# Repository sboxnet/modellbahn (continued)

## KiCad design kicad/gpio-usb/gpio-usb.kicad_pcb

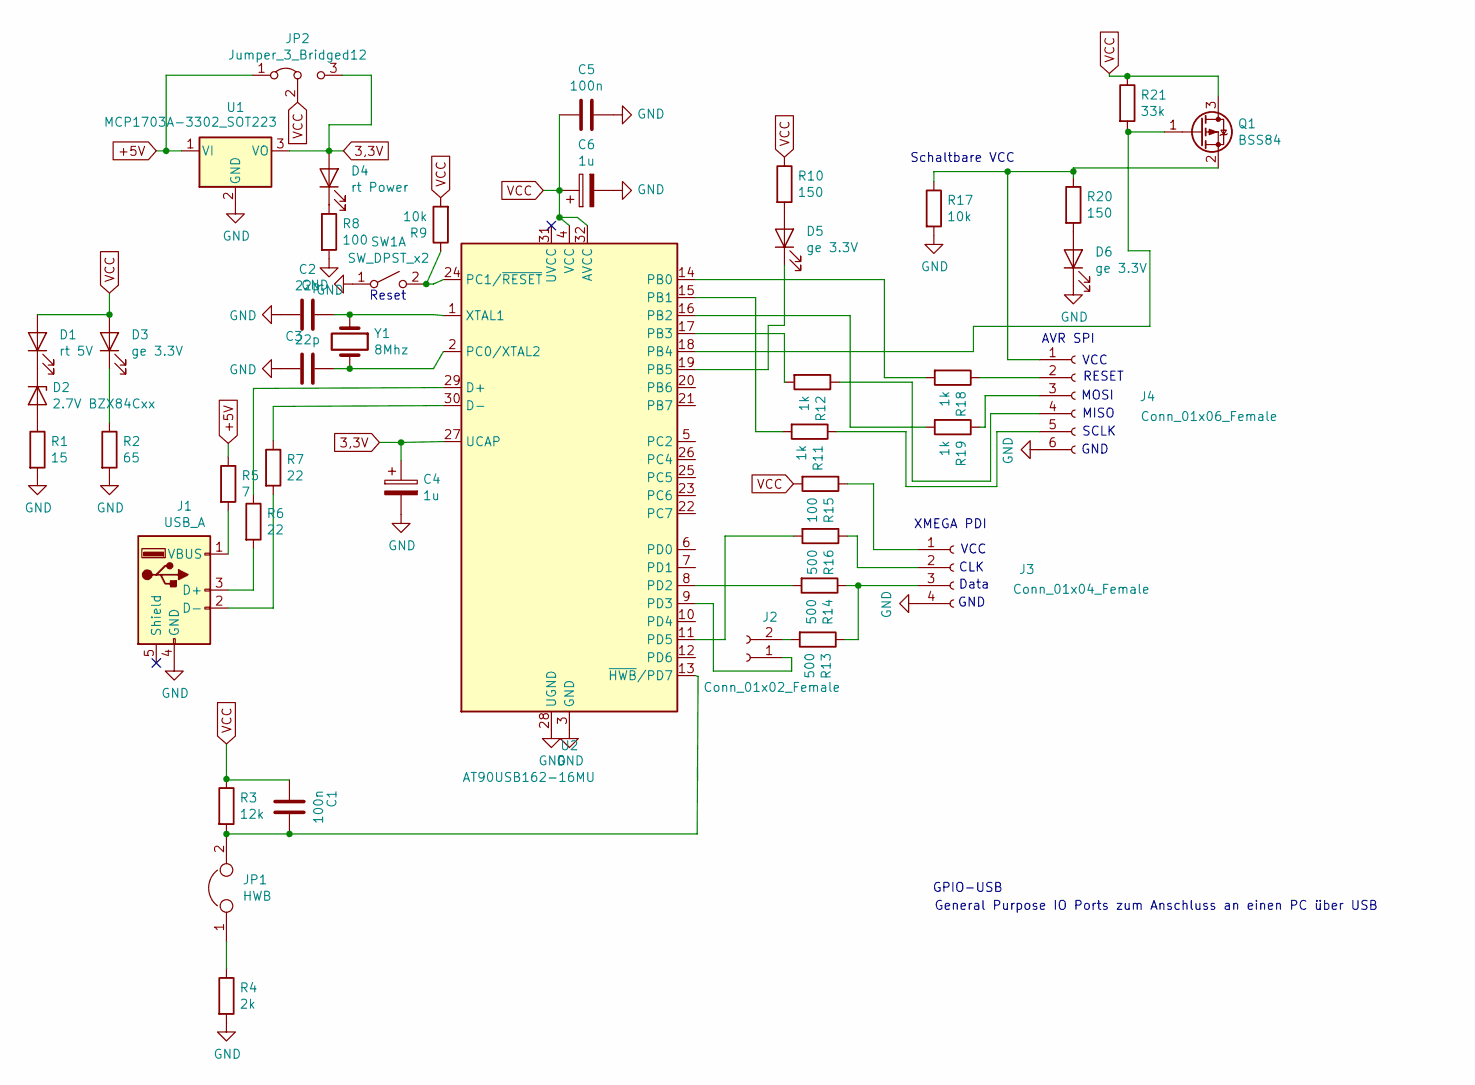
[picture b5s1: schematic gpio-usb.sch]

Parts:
C1: 100n; C_1206_3216Metric_Pad1.42x1.75mm_HandSolder
C2, C3: 22p; C_1206_3216Metric_Pad1.42x1.75mm_HandSolder
C4, C6: 1u; smd_cap_1206
C5: 100n; C_1206_3216Metric
D1: rt 5V; LED_0805_2012Metric
D2: 2.7V BZX84Cxx; D_SOT-23_ANK
D3, D5, D6: ge 3.3V; LED_0805_2012Metric
D4: rt Power; LED_0805_2012Metric
J1: USB_A; usbaassmann
J2: Conn_01x02_Female; PinHeader_1x02_P2.54mm_Vertical
J3: Conn_01x04_Female; PinHeader_1x04_P2.54mm_Vertical
J4: Conn_01x06_Female; PinHeader_1x06_P2.54mm_Vertical
JP1: HWB; jumper_2_male
JP2: Jumper_3_Bridged12; jumper_3_female
Q1: BSS84; SOT-23
R1: 15; R_1206_3216Metric
R2: 65; R_1206_3216Metric
R3: 12k; R_1206_3216Metric
R4: 2k; R_1206_3216Metric
R5: 7; R_1206_3216Metric
R6, R7: 22; R_1206_3216Metric
R8, R15: 100; R_1206_3216Metric
R9, R17: 10k; R_1206_3216Metric
R10, R20: 150; R_1206_3216Metric
R11, R12, R18, R19: 1k; R_1206_3216Metric
R13, R14, R16: 500; R_1206_3216Metric
R21: 33k; R_1206_3216Metric
SW1: SW_DPST_x2; PinHeader_1x02_P2.54mm_Vertical
U1: MCP1703A-3302_SOT223; SOT-223-3_TabPin2
U2: AT90USB162-16MU; QFN-32-1EP_5x5mm_P0.5mm_EP3.6x3.6mm
Y1: 8Mhz; Crystal_HC33-U_Vertical

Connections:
3,3V: C4.1, D4.2 (A), JP2.3 (B), U1.3 (VO), U2.27 (UCAP)
+5V: JP2.1 (A), R5.1, U1.1 (VI)
GND: C2.2, C3.2, C4.2, C5.1, C6.2, D6.1 (K), J1.4 (GND), J3.4, J4.6, R1.2, R2.2, R4.2, R8.2, R17.2, SW1.1 (A), U1.2 (GND), U2.3 (GND), U2.28 (UGND), U2.33 (GND)
unnamed: C1.1, JP1.2, R3.2, U2.13 (~HWB~/PD7)
unnamed: C2.1, U2.1 (XTAL1), Y1.1
unnamed: C3.1, U2.2 (PC0/XTAL2), Y1.2
unnamed: D1.1 (K), D2.1 (K)
unnamed: D2.2 (A), R1.1
unnamed: D3.1 (K), R2.1
unnamed: D4.1 (K), R8.1
unnamed: D5.1 (K), U2.19 (PB5)
unnamed: D5.2 (A), R10.2
unnamed: D6.2 (A), R20.2
unnamed: J1.1 (VBUS), R5.2
unnamed: J1.2 (D-), R7.2
unnamed: J1.3 (D+), R6.2
unnamed: J2.1, U2.9 (PD3)
unnamed: J2.2, R13.2
unnamed: J3.1, R15.1
unnamed: J3.2, R16.1
unnamed: J3.3, R13.1, R14.1
unnamed 22: J4.1, Q1.2 (S), R17.1, R20.1; also elsewhere on the board
unnamed: J4.2, R18.1
unnamed: J4.3, R19.1
unnamed: J4.4, R12.1
unnamed: J4.5, R11.1
unnamed: JP1.1, R4.1
unnamed: Q1.1 (G), R21.2, U2.18 (PB4)
unnamed: R6.1, U2.29 (D+)
unnamed: R7.1, U2.30 (D-)
unnamed: R9.1, SW1.2 (B), U2.24 (PC1/~RESET)
unnamed: R11.2, U2.15 (PB1)
unnamed: R12.2, U2.17 (PB3)
unnamed: R14.2, U2.8 (PD2)
unnamed: R16.2, U2.11 (PD5)
unnamed: R18.2, U2.14 (PB0)
unnamed: R19.2, U2.16 (PB2)
VCC: C1.2, C5.2, C6.1, D1.2 (A), D3.2 (A), JP2.2 (C), Q1.3 (D), R3.1, R9.2, R10.1, R15.2, R21.1, U2.4 (VCC), U2.32 (AVCC); also elsewhere on the board

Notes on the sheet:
Reset
GND
Data
CLK
VCC
XMEGA PDI
GPIO-USB
General Purpose IO Ports zum Anschluss an einen PC über USB
Schaltbare VCC
RESET
MOSI
MISO
SCLK
AVR SPI

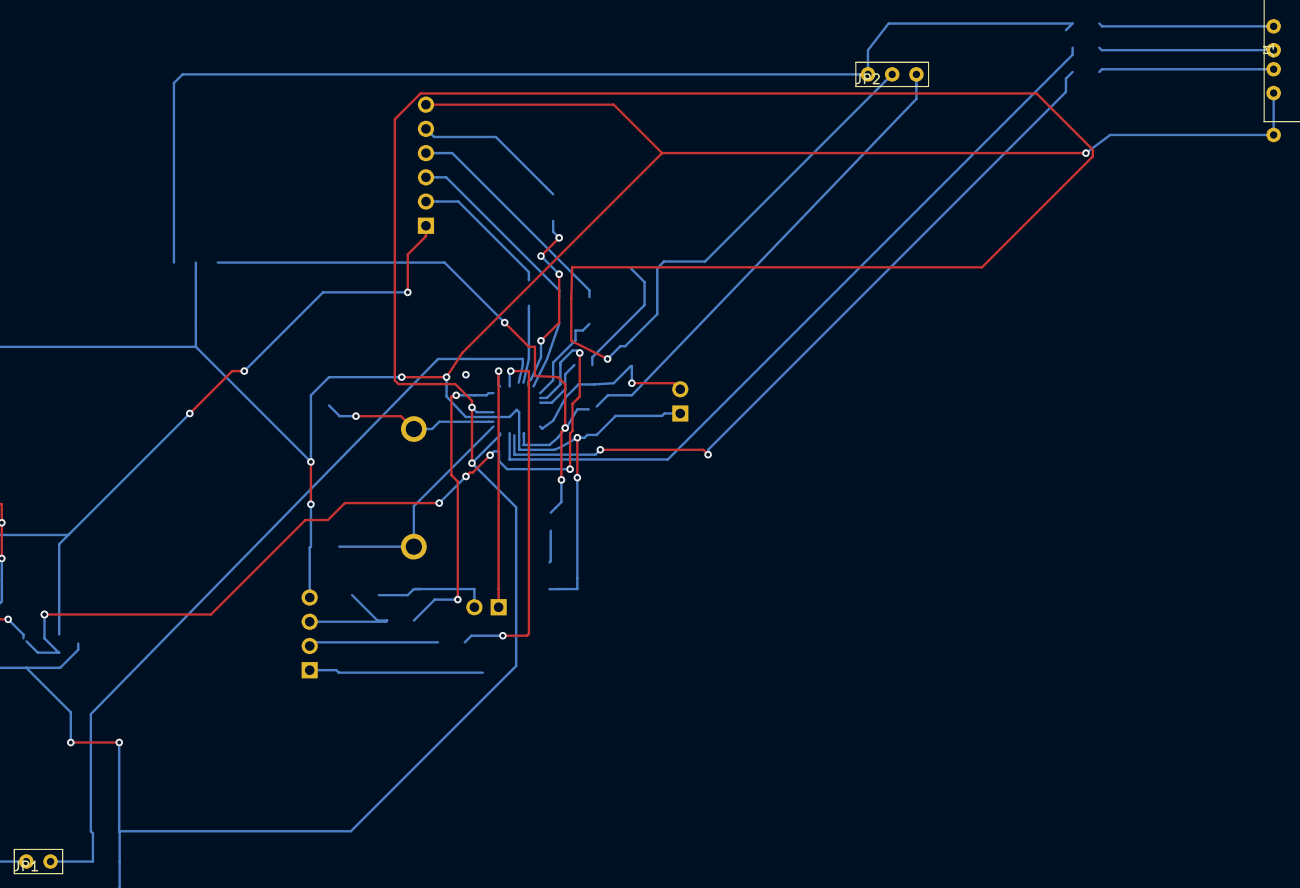
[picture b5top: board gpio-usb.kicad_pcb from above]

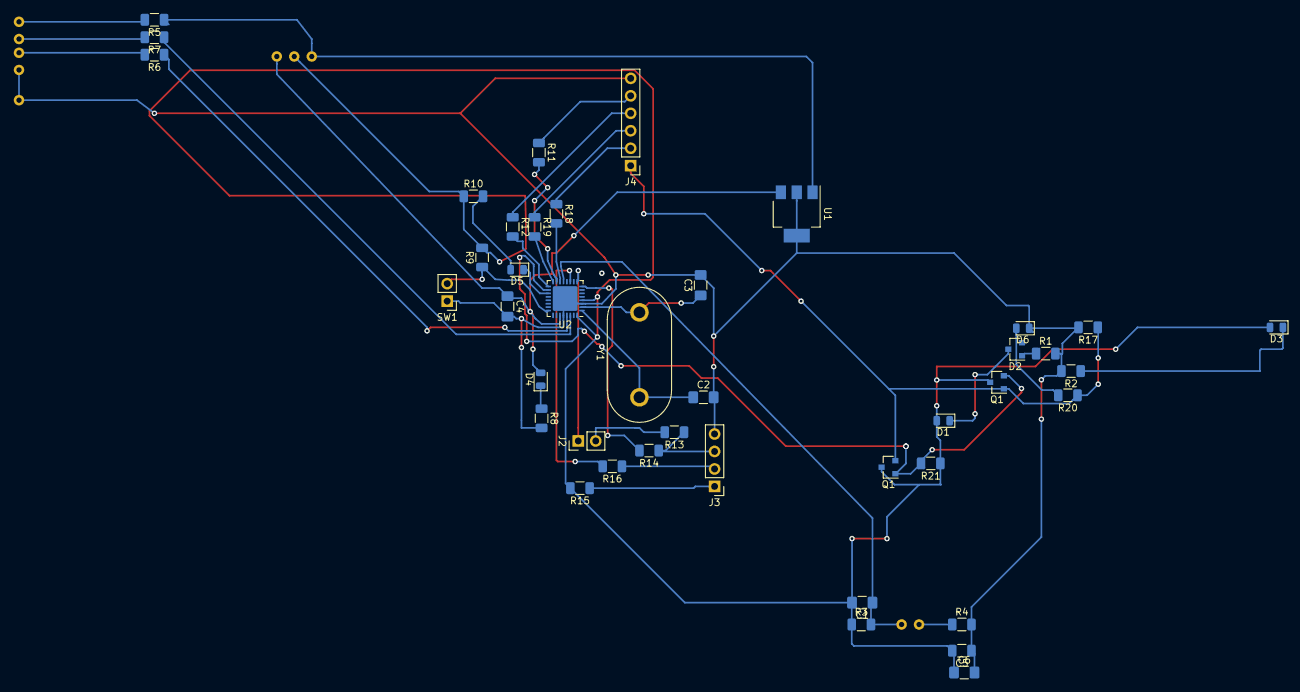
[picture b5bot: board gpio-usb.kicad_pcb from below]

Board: 2 copper layers, 45 parts (42 on the bottom side), 38 nets.

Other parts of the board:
Q1#2: BSS138; SOT-23

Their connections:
unnamed 22: Q1#2.1; also elsewhere on the board
VCC: Q1#2.3; also elsewhere on the board

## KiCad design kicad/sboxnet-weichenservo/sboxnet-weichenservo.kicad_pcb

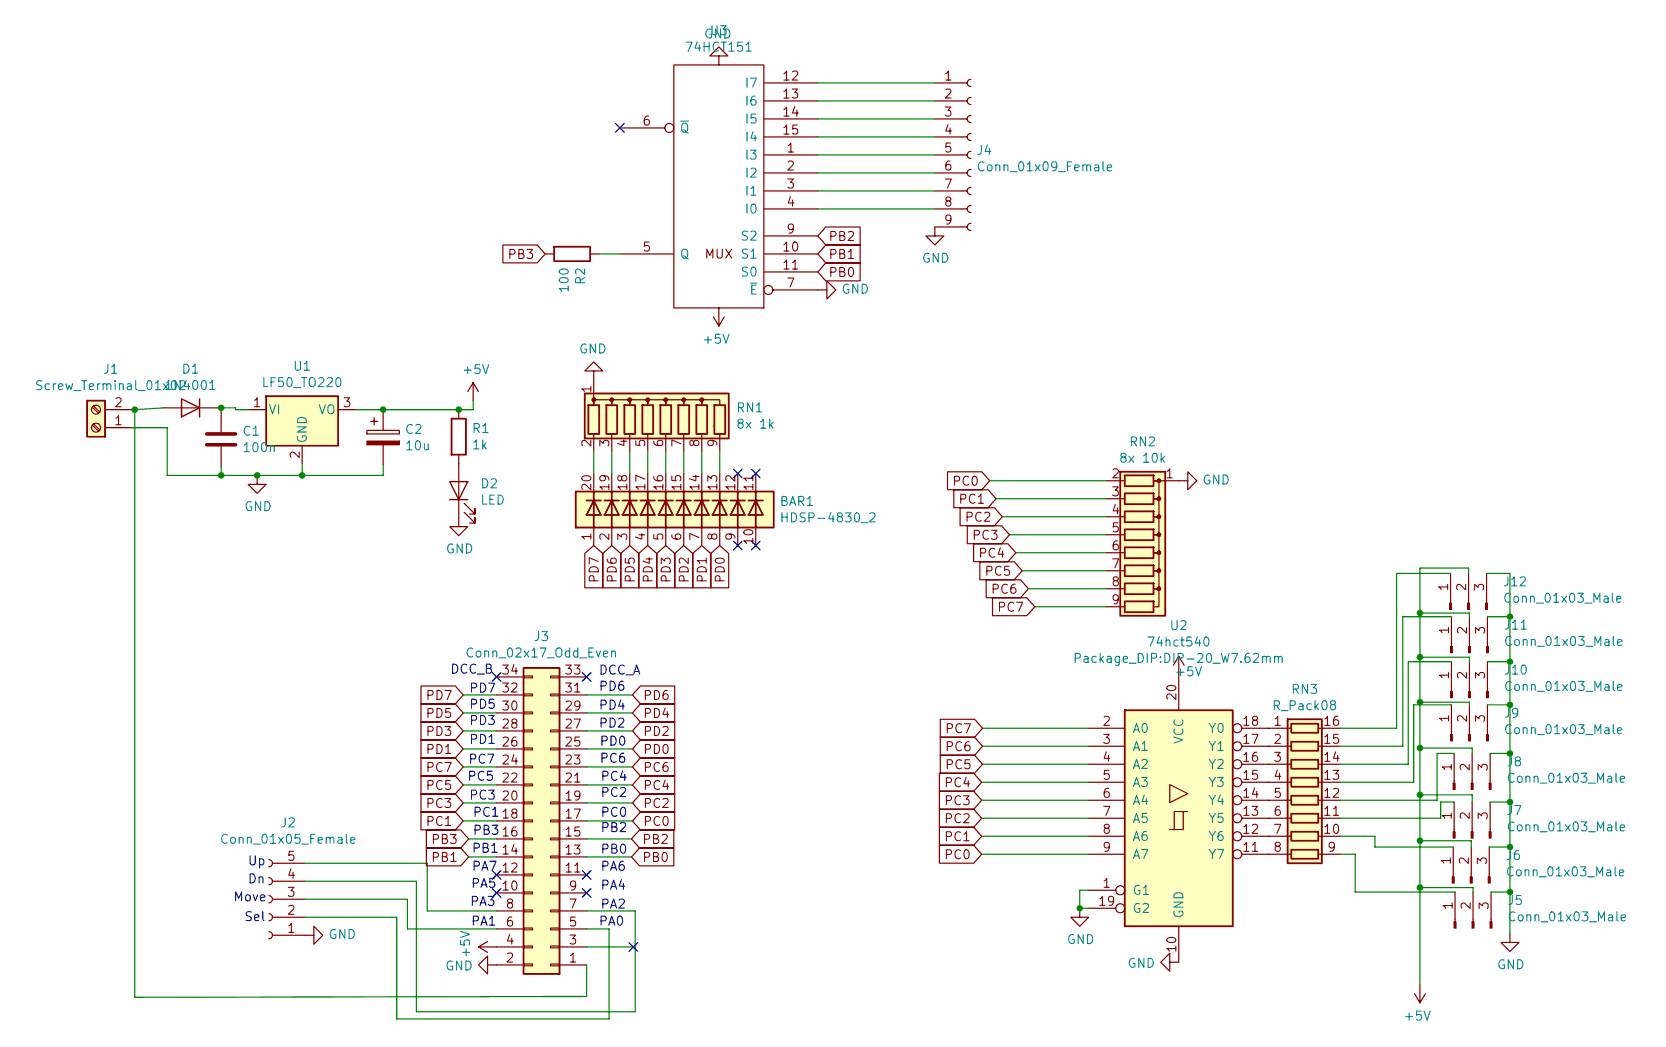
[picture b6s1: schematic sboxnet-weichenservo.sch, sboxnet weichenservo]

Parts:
BAR1: HDSP-4830_2; HDSP-4830
C1: 100n; C_Axial_L3.8mm_D2.6mm_P7.50mm_Horizontal
C2: 10u; CP_Axial_L10.0mm_D4.5mm_P15.00mm_Horizontal
D1: 1N4001; D_DO-41_SOD81_P10.16mm_Horizontal
D2: LED; LED_D3.0mm
J1: Screw_Terminal_01x02; TerminalBlock_Altech_AK300-2_P5.00mm
J2: Conn_01x05_Female; PinSocket_1x05_P2.54mm_Vertical
J3: Conn_02x17_Odd_Even; sboxnet-stecker-2x17
J4: Conn_01x09_Female; PinHeader_1x09_P2.54mm_Vertical
J5, J6, J7, J8, J9, J10, J11, J12: Conn_01x03_Male; PinHeader_1x03_P2.54mm_Vertical
R1: 1k; R_Axial_DIN0204_L3.6mm_D1.6mm_P5.08mm_Vertical
R2: 100; R_Axial_DIN0207_L6.3mm_D2.5mm_P5.08mm_Vertical
RN1: 8x 1k; R_Array_SIP9
RN2: 8x 10k; R_Array_SIP9
RN3: R_Pack08; DIP-16_W7.62mm
U1: LF50_TO220; TO-220-3_Vertical
U2: 74hct540; DIP-20_W7.62mm
U3: 74HCT151; DIP-16_W7.62mm_Socket

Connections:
+5V: C2.1, J3.4, J5.2, J6.2, J7.2, J8.2, J9.2, J10.2, J11.2, J12.2, R1.1, U1.3 (VO), U2.20 (VCC), U3.16 (VCC)
GND: C1.2, C2.2, D2.1 (K), J1.1, J2.1, J3.2, J4.9, J5.3, J6.3, J7.3, J8.3, J9.3, J10.3, J11.3, J12.3, RN1.1 (common), RN2.1 (common), U1.2 (GND), U2.1 (G1), U2.10 (GND), U2.19 (G2), U3.7 (~E), U3.8 (GND)
unnamed: BAR1.13 (K), RN1.9 (R8)
unnamed: BAR1.14 (K), RN1.8 (R7)
unnamed: BAR1.15 (K), RN1.7 (R6)
unnamed: BAR1.16 (K), RN1.6 (R5)
unnamed: BAR1.17 (K), RN1.5 (R4)
unnamed: BAR1.18 (K), RN1.4 (R3)
unnamed: BAR1.19 (K), RN1.3 (R2)
unnamed: BAR1.20 (K), RN1.2 (R1)
unnamed: C1.1, D1.1 (K), U1.1 (VI)
unnamed: D1.2 (A), J1.2, J3.1
unnamed: D2.2 (A), R1.2
unnamed: J2.2, J3.5
unnamed: J2.3, J3.6
unnamed: J2.4, J3.7
unnamed: J2.5, J3.8
unnamed: J4.1, U3.12 (I7)
unnamed: J4.2, U3.13 (I6)
unnamed: J4.3, U3.14 (I5)
unnamed: J4.4, U3.15 (I4)
unnamed: J4.5, U3.1 (I3)
unnamed: J4.6, U3.2 (I2)
unnamed: J4.7, U3.3 (I1)
unnamed: J4.8, U3.4 (I0)
unnamed: J5.1, RN3.9 (R8.2)
unnamed: J6.1, RN3.10 (R7.2)
unnamed: J7.1, RN3.11 (R6.2)
unnamed: J8.1, RN3.12 (R5.2)
unnamed: J9.1, RN3.13 (R4.2)
unnamed: J10.1, RN3.14 (R3.2)
unnamed: J11.1, RN3.15 (R2.2)
unnamed: J12.1, RN3.16 (R1.2)
unnamed: R2.1, U3.5 (Q)
unnamed: RN3.1 (R1.1), U2.18 (Y0)
unnamed: RN3.2 (R2.1), U2.17 (Y1)
unnamed: RN3.3 (R3.1), U2.16 (Y2)
unnamed: RN3.4 (R4.1), U2.15 (Y3)
unnamed: RN3.5 (R5.1), U2.14 (Y4)
unnamed: RN3.6 (R6.1), U2.13 (Y5)
unnamed: RN3.7 (R7.1), U2.12 (Y6)
unnamed: RN3.8 (R8.1), U2.11 (Y7)
PB0: J3.13, U3.11 (S0)
PB1: J3.14, U3.10 (S1)
PB2: J3.15, U3.9 (S2)
PB3: J3.16, R2.2
PC0: J3.17, RN2.2 (R1), U2.9 (A7)
PC1: J3.18, RN2.3 (R2), U2.8 (A6)
PC2: J3.19, RN2.4 (R3), U2.7 (A5)
PC3: J3.20, RN2.5 (R4), U2.6 (A4)
PC4: J3.21, RN2.6 (R5), U2.5 (A3)
PC5: J3.22, RN2.7 (R6), U2.4 (A2)
PC6: J3.23, RN2.8 (R7), U2.3 (A1)
PC7: J3.24, RN2.9 (R8), U2.2 (A0)
PD0: BAR1.8 (A), J3.25
PD1: BAR1.7 (A), J3.26
PD2: BAR1.6 (A), J3.27
PD3: BAR1.5 (A), J3.28
PD4: BAR1.4 (A), J3.29
PD5: BAR1.3 (A), J3.30
PD6: BAR1.2 (A), J3.31
PD7: BAR1.1 (A), J3.32

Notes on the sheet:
PA0
PA2
PA4
PA6
PB0
PB2
PC0
PC2
PC4
PC6
PD0
PD2
PD4
PD6
DCC_A
PA1
PA3
PA5
PA7
PB3
PC1
PC3
PC5
PC7
PD1
PD3
PD5
PD7
DCC_B
Move
Sel
PB1

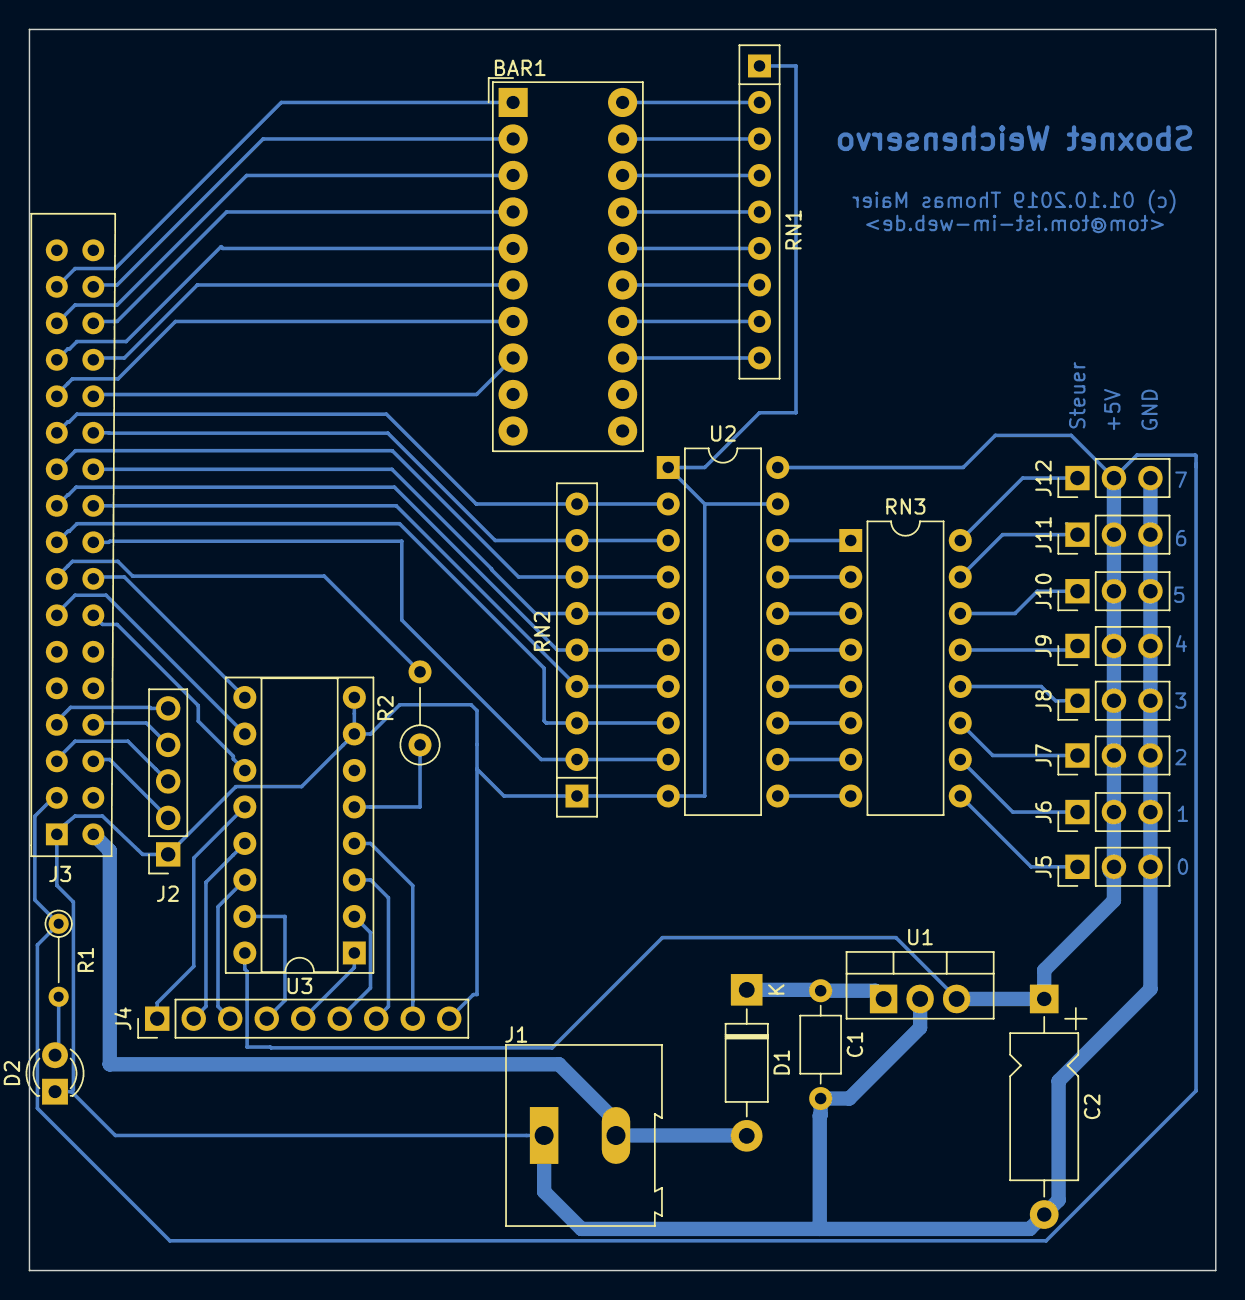
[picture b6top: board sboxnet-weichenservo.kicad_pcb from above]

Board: 2 copper layers, 82.5 x 86.4 mm, 25 parts (0 on the bottom side), 62 nets.

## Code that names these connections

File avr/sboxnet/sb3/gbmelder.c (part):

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
// für neue Hardware!
void show_besetzt_leds(void) {
	// PC6 (Bit 0) und PC7 (Bit 1)
	// PD0..PD7(Bit 2 .. 9)
	// zuerst mal alles aus
	port_clr(PORTC, Bit(6)|Bit(7));
	port_out(PORTD) = 0;
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
void do_init_system(void) {
	// Erst Hardware prüfen
	// PORTB auf Input: PB0..PB3
	port_dirin(PORTB, 0x0f);
	// und Eingabe überprüfen
	uint8_t pbin = port_in(PORTB);
	// ist PB0 und PB2 auf Low, PB1 und PB3 auf High ==> neue Hardware
	if (bit_is_set(pbin, 2) && bit_is_clear(pbin, 1) && bit_is_clear(pbin, 3)) {
		// neue Hardware
		hardwaretyp = 1;
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	switch(hardwaretyp) {
		case 1: {
            // Port für LEDs: im Gegensatz zur alten Hardware wird hier nicht multiplexed, sondern direkt LEDs angesteuert
            // PD0..PD7(Bit 2 .. 9)
			port_out(PORTD) = 0; // PORTD = 0
			port_dirout(PORTD, 0xff); // PORTD as output
			PORTCFG_MPCMASK = 0xff; // Alle Pins
			PORTD.PIN0CTRL = PORT_OPC_TOTEM_gc; // Alle PORTD Pins auf TOTEM Pole
			// PC6 (Bit 0) und PC7 (Bit 1)
			port_dirout(PORTC, Bit(6) | Bit(7)); // PC6 and PC7 as output
            PORTCFG_MPCMASK = 0xc0;
            PORTC.PIN0CTRL = PORT_OPC_TOTEM_gc;

            // PORTA als Input (PA0..PA7) (Bit 0 .. 7)
            port_dirin(PORTA, 0xff);
            // PC0 (Bit 8), PC1 (Bit 9) als Eingabe
            port_dirin(PORTC, 0x3);

			break;
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    // Sensoren Init mit 0 == Nichts belegt
    memset(g_sensors, 0, sizeof(g_sensors));
    
    // PB0  DCC Signal Pin

    // PB0 PullDown, beide Flanken
    DCCSENSE_PORT.PIN0CTRL = PORT_OPC_PULLDOWN_gc|PORT_ISC_BOTHEDGES_gc;
    //PORTB.PIN0CTRL = PORT_OPC_PULLDOWN_gc|PORT_ISC_BOTHEDGES_gc;
    // Decoder Init PortB0
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
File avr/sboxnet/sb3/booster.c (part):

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// LED Port
#define LED_PORT  PORTD
// Bits für LEDs
#define LED_NOTAUS_b      0 // Notaus
#define LED_CUR_OV_b      1 // Strom zu hoch
#define LED_CUR_SHORT_b   2 // Kurzschluss
#define LED_BO_ON_b       3 // Booster EIN
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#define DCCM_IN2_b  1 // IN2
#define DCCM_OV_b   3 // OV
#define DCCM_DCCIN_b  4
#define DCCM_NOTAUS_b 5 // NOTAUS
//#define DCCM_CUTOUT_b 7

// Strom zu hoch detektor: PORT
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//#define CUR_OV_b   3

// Booster NOTAUS betätigt: PORT
//#define NOTAUS_PORT  PORTC
// und Bit:
//#define NOTAUS_b   5

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// g_advals[2] Booster Strom 2
static uint16_t g_advals[3] = { 0, 0, 0 };

// Notaus PC5
#define SWITCH_NOTAUS_b  0
// Button zwischenspeichern für Entprellung
static uint8_t g_switches = 0;
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
// Booster Flags
#define BOOSTER_FLG_ON_b      0 // Booster ist EIN
#define BOOSTER_FLG_NOTAUS_b  1 // Booster NOTAUS
#define BOOSTER_FLG_CUR_OV_b  2 // Booster Strom zu hoch
static uint8_t g_booster_flags = 0; // Booster Flags

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 * Kurzschluss Sensor aus
 */
void dcc_sensors_off(void) {
    // PC3 Sensor Interrupt aus: PORTC INT0
    DCCM_PORT.INTCTRL = (PORTC.INTCTRL & ~PORT_INT0LVL_gm) | PORT_INT0LVL_OFF_gc;
    // Kein PORTC INT0 mehr
    DCCM_PORT.INT0MASK = 0; // L6206 Stromüberwachung
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    DCCM_PORT.INTFLAGS = Bit(PORT_INT0IF_bp); // clear interrupt flags;
    
    DCCM_PORT.INTCTRL = (PORTC.INTCTRL & ~PORT_INT0LVL_gm) | PORT_INT0LVL_OFF_gc;
    // DCCM_OV_b (PC3) auf Falling Edge
    DCCM_PORT.PIN3CTRL = PORT_ISC_FALLING_gc;
    
    // Anzahl Kurzschlüsse zurücksetzen
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        // DCC IN Interrupt
        // DCCM_PORT.DCCM_DCCIN_b als PORTC Int1
        DCCM_PORT.INT1MASK = Bit(DCC_IN_b);
        // PC4 beidseitige Flanke
        DCCM_PORT.PIN4CTRL = PORT_ISC_BOTHEDGES_gc;
        // INT1 Flag löschen
        DCCM_PORT.INTFLAGS = Bit(PORT_INT1IF_bp);
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        g_timer_startup = TIMER_STARTUP;

        // DCC IN Init
        // Status von PC4 (DCCM_IN_b) H?
        if (bit_is_set(port_in(DCC_IN_PORT), DCC_IN_b)) {
            // dann Brücke init mit
            port_setbit(DCCM_PORT, DCCM_IN1_b); // IN1 als H
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    port_clrbit(LED_PORT, LED_NOTAUS_b);
}

/* Port PC3 (Stromabschaltung)
 * 
 * Kurzschluss LED kurz aufleuchten, Kurzschlusszähler erhöhen.
 */
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 * DCC Signal aus.
 */
static NOINLINE void dcc_signal_disable(void) {
    // Bit DCCM_EN_b (PC2) aus
    port_clrbit(DCCM_PORT, DCCM_EN_b);
    // 2us warten
    _delay_us(2);
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static NOINLINE void dcc_signal_enable(void) {
    // 1us warten
    _delay_us(1);
    // Bit DCCM_EN_b (PC2) ein
    port_setbit(DCCM_PORT, DCCM_EN_b);
}

/* DCC Input Signal: PORTC.PC4 port Interrupt
 * PORTC.PC4 reagiert auf beide Flanken.
 *
 */
ISR(PORTC_INT1_vect) { // DCC Input Signal
    // ist PORTC.PC4 gesetzt?
    if (bit_is_set(port_in(DCC_IN_PORT), DCC_IN_b)) {
        // webb H, dann erst disable
        dcc_signal_disable();
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
/* void measure_task(void)
 * Durchführung der Strom und Spannungsmessung.
 * PA0, PA2 Strommessung: U = 0.22 * I; 0.22 * 1A = 0.22 V, 0.22 * 2A = 0.44V, 0.22 * 3A = 0.66V: 0,22 * 2.4A= 0,528V
 *     bei Rcl = 10kOhm Stromabschaltung bei ca 2,3 A
 * PA1 Spannungsmessung Vmess = 0.05982 * V bei 15 V -> 0,8974 V
 */
static void measure_task(void) {
    // sind alle ADCA Kanele bereit
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    // LED_PORT auf Ausgabe
    port_dirout(PORTD, 0x0f);
    // LED_PORTs auf totem pole
    PORTCFG_MPCMASK = 0x0f; // PD2..0
    PORTD.PIN0CTRL = PORT_OPC_TOTEM_gc;
    
    // DCCM_PORT
    // alles OFF vorbereiten
    port_out(DCCM_PORT) = 0;
    // PC0 (IN1), PC1(IN2), PC2 (EN) als Ausgabe
    port_dirout(DCCM_PORT, Bit(DCCM_EN_b)|Bit(DCCM_IN2_b)|Bit(DCCM_IN1_b));
    // PC3(OV), PC4 (DCCIN), PC5(NOTAUS) als Eingabe
    port_dirin(DCCM_PORT, Bit(DCCM_OV_b)|Bit(DCCM_DCCIN_b)|Bit(DCCM_NOTAUS_b));
    // Ausgabe ports als totem pole
    PORTCFG_MPCMASK = Bit(DCCM_EN_b)|Bit(DCCM_IN2_b)|Bit(DCCM_IN1_b);
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
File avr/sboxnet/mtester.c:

#include "common.h"
#include "sboxnet-struct.h"

#define DEVICE_DESC "ModulTester"
#define PRODUCT_ID   0xa123
#define VENDOR_ID    0x5566
#define FIRMWARE_VERSION 0x0200


APP_FIRMWARE_HEADER(PRODUCT_ID, VENDOR_ID, FIRMWARE_VERSION)

/* timer TCC1
 */

#define TIMER_PERIOD (32000000 / 1024 -1) // = 31250-1

#define NUM_STEPS 3
// wird bei jedem TCC0 OV um eins verringert
volatile int8_t step = NUM_STEPS-1;

// TCC0 overflow 
ISR(TCC1_OVF_vect) {
    step--;
    if (step < 0) {
        step = NUM_STEPS-1;
    }
}


// do_init_system: device system init
// return none
void do_init_system(void) {
    // alle Ports auf Output
    port_out(PORTA) = 0x0;
    port_dirout(PORTA, 0xff); // PORTA as output
    PORTCFG_MPCMASK = 0xff;
    PORTA.PIN0CTRL = PORT_OPC_TOTEM_gc; // all PORTA Pins to TOTEM 
    
    port_out(PORTB) = 0x0;
    port_dirout(PORTB, 0xff); // PORTB as output
    PORTCFG_MPCMASK = 0xff; // all pin
    PORTB.PIN0CTRL = PORT_OPC_TOTEM_gc; // all PORTB Pins to TOTEM 
    
    port_out(PORTC) = 0x0;
    port_dirout(PORTC, 0xff); // PORTC as output
    PORTCFG_MPCMASK = 0xff; // all pin
    PORTC.PIN0CTRL = PORT_OPC_TOTEM_gc; // all PORTC Pins to TOTEM 
    
    port_out(PORTD) = 0x0;
    port_dirout(PORTD, 0xff); // PORTD as output
    PORTCFG_MPCMASK = 0xff; // all pin
    PORTD.PIN0CTRL = PORT_OPC_TOTEM_gc; // all PORTD Pins to TOTEM
    
    //port_set(PORTD, Bit(5));
    //port_set(PORTD, Bit(4));
    
    // set paramters written to EEPROM from common area g_com
    // set Product ID
    g_com.productid = PRODUCT_ID;
    // set VENDOR_ID
    g_com.vendorid = VENDOR_ID;
    // set Firmware Version
    g_com.firmware_version = FIRMWARE_VERSION;
    // Fähigkeiten
    g_com.capabilities = CAP_TESTER;
    // Fähigkeit.Klasse
    g_com.cap_class = 0;
    // Gerätebeschreibung
    g_com.dev_desc_P = PSTR(DEVICE_DESC);
    
    // timer 16bit TCC0
    TCC1.CTRLB = TC_WGMODE_NORMAL_gc;
    TCC1.CTRLD = 0;
    TCC1.CTRLE = 0;
    // timer overflow 
    TCC1.INTCTRLA = TC_OVFINTLVL_LO_gc;
    TCC1.INTCTRLB = 0;
     // clear all interupts
    TCC1.INTFLAGS = 0xff;
    // periode
    TCC1.PER = TIMER_PERIOD; 
    
    // enable with /1024
    TCC1.CTRLA = TC_CLKSEL_DIV1024_gc;
    
    port_set(PORTD, 0x30);
    port_clr(PORTD, 0xc0);
    
    // enable clkout pd7
    //port_dirout(PORTD, Bit(7));
    //PORTCFG.CLKEVOUT = PORTCFG_CLKOUT_PD7_gc;
    
    return;
}

// do_reg_read: read a register (reg: 16bit register, pdata: pointer to data)
// return a SBOXNET_ACKRC_* retcode
uint8_t do_reg_read(uint16_t reg, uint16_t* pdata) {
    return SBOXNET_ACKRC_REG_INVALID;
}

// do_reg_write: write a register (reg: 16 bit register, data: 16 bit data, mask: 16 bit maske)
// return a SBOXNET_ACKRC_* retcode
uint8_t do_reg_write(uint16_t reg, uint16_t data, uint16_t mask) {
    return SBOXNET_ACKRC_REG_INVALID;
}

// do_msg: process a message pmsg: pointer to a struct sboxnet_msg_header
// return a SBOXNET_ACKRC_* retcode
uint8_t do_msg(struct sboxnet_msg_header *pmsg) {
    return SBOXNET_ACKRC_CMD_UNKNOWN;
}

// do_setup: init the device user defined
// return none
void do_setup(void) {
    sei();
    return;
}

void exec_step0();
void exec_step1();
void exec_step2();


// do_main: Hauptroutine
// wird periodisch aufgerufen
// return none

void do_main(void) {
    sei();
    
    //PORTA = 

    //exec_step2();
    //exec_step1();
    //exec_step2();
    //step=3;
    
    //exec_step2();
    //step = 0;
    //port_out(PORTA) = 0;
    //Sport_out(PORTC) = 0x10;
    
    switch(step)
    {
        case 0:
        {
            exec_step0();
            //step++;
            break;
        }
        case 1:
        {
            exec_step1();
            //step++;
            break;
        }
        case 2:
        {
            exec_step2();
            //step++
            break;
        }
        default:
            break;
    }
    //for(;;) ;
    
    return;
}

// do_before_bldr_activate: Statements die vor der Aktivierung des Bootloaders ausgeführt werden sollen
// return none
void do_before_bldr_activate(void) {
    // nothing
    return;
}


void exec_step0() {
    // first porta auf alle HIGH
    port_out(PORTA) = 0xff;
    // PC* auf LOW
    port_out(PORTC) = 0;
    
    port_out(PORTB) = 0xff; // PB all 1
    port_clr(PORTD, 0x0f); // PD0..3 auf LOW
    
    port_set(PORTD, 0x30); // PD4..5 H
    port_clr(PORTD, 0xc0); // PD6..7 L
}

void exec_step1() {
    // first porta auf alle L
    port_out(PORTA) = 0;
    // PC* auf H
    port_out(PORTC) = 0xff;
    
    port_out(PORTB) = 0; // PB all 0
    port_set(PORTD, 0x0f); // PD0..3 auf H
    
    port_clr(PORTD, 0x30); // PD4..5 L
    port_set(PORTD, 0xc0); // PD6..7 H
}

void exec_step2() {
    // first porta auf  00001111
    port_out(PORTA) = 0x0f;
    // PC* auf 11110000
    port_out(PORTC) = 0xf0;
    
    port_out(PORTB) = 0; // PB all 0
    port_set(PORTD, 0x0f); // PD0..3 auf H
    
    port_clr(PORTD, 0x30); // PD4..5 L
    port_set(PORTD, 0xc0); // PD6..7 H
    /*port_clr(PORTD, Bit(5));
    port_clr(PORTD, Bit(4));
    */
}

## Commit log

2020-07-12 README
2020-07-12 KICAD Modules
2020-07-12 add files for programmer, libtmb, avr
2020-07-12 fixedREADME
2020-07-13 fixed booster L6206PSO
2020-07-13 update booster kicad
2020-07-13 update booster layout with POWERSO Slug Down Terminal Vias
2020-07-13 fixed
2020-07-14 PSO backplane
2020-07-14 with gerber
2020-07-14 add heatsink footprint
2020-07-15 work in progress layout
2020-07-15 layout LEDs
2020-07-16 finished booster layout
2020-07-17 sboxnet booster finished
2020-07-18 booster DCC Input
2020-07-19 Docu von Booster
2020-07-19 GBmelder
2020-07-20 sboxnet Studio 7 Project
2020-07-21 gbmelder_fixed
2020-07-23 UpdateGBmelder
2020-07-24 standardtimerD0
2020-07-24 cleanup
2020-07-24 Timer D0 Doku
2020-07-25 removed __pycache__ from git
2020-07-25 show_besetzt_leds
2020-07-28 fixed LED ports
2020-08-01 sbntst initial
2020-08-01 sbntst
2020-08-04 add railcom spec
2020-08-07 update DCC List
2020-08-07 link to moba-dcc.csv
2020-08-07 add python usb
2020-08-07 test
2020-08-07 cleanup moba-dcc
2020-08-09 plot pcbs
2020-08-09 new sboxnet tester
2020-08-12 with wing project
2020-08-13 send in a loop: cmd_net_reset
2020-08-14 SBOXNET_CMD_DEV_REQ_ADDR works
2020-08-15 request address
2020-08-16 fixed SboxnetUSB.getserialnumber()
2020-08-17 add logon
2020-08-17 getserialnumber
2020-08-17 more cmds
2020-08-18 devgetdesc
2020-08-19 for devgetdesc wait a little bit before input again to let answer be processed
2020-08-19 watchdog, no answer from device, more cmds
2020-08-19 cmd reg *
2020-08-20 fixed Bug in gbmelder
2020-08-20 sbntst fertig
2020-08-21 Pull Ups for inputs
2020-08-22 do not print Watchdog msg
2020-08-22 do not ignore Sig INT
2020-08-22 print -> logDebug
2020-08-22 do not print watchdog rc msgs
2020-08-22 NET_WATCHDOG verbessert
2020-08-23 vs add booster-raw.c and dccgen.c
2020-08-23 sbntst fixed, makefile for booster-raw + dccgen, common booster shortcut detector
2020-08-30 dccgen remove watchdog test for on/off
2020-08-30 booster cleanup, sboxnet-booster add on led
2020-08-30 cleanup booster-raw and dccgen, add booster on led
2020-09-06 fixed booster schema
2020-09-06 ein Test
2020-09-06 undo Test
2020-09-06 booster anpassungen
2020-09-14 Mehr docu
2020-09-18 mit altem booster code
2020-09-20 booster neu gemacht
2020-09-27 new booster code
2020-09-27 new booster 20200927
2020-10-11 20201011
2020-10-31 20201031
2020-10-31 20201031-2
2021-01-07 atmel studio for sboxnet2usb, boot loader switch_to_32MHz
2021-01-07 reset sboxnet to work without avr_mega, fixed usb.c for -g3
2021-01-19 sboxnet modul v4
2021-01-21 correct sboxnet-modul
2021-03-13 cleanup 20210313
